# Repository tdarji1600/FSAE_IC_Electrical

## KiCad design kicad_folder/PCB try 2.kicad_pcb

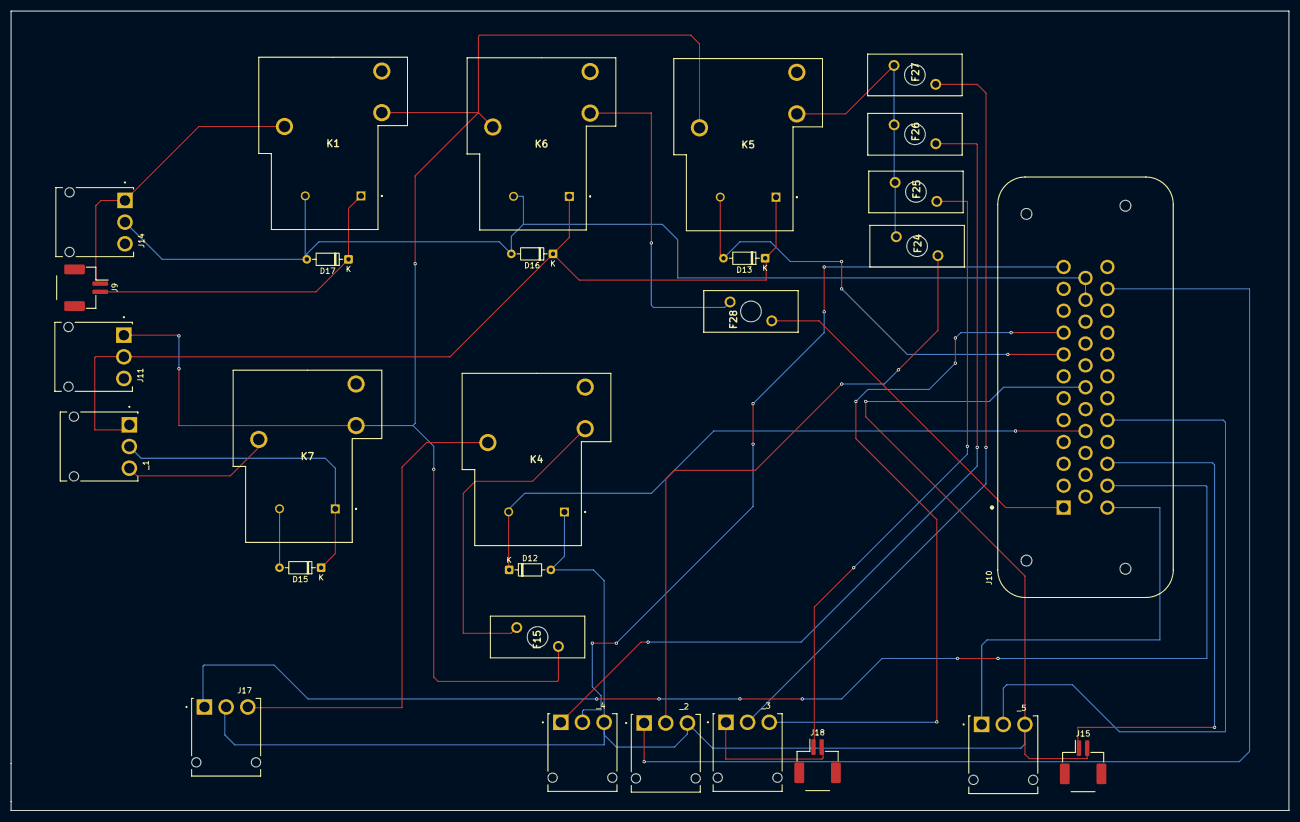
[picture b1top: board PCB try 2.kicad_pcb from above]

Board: 2 copper layers, 233.7 x 146.2 mm, 28 parts (0 on the bottom side), 28 nets.

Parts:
D12, D13, D15, D16, D17: D; D_DO-35_SOD27_P7.62mm_Horizontal
F15: Fans 5A; Little Fuse (01530008)
F24: O2 heater 10A; Little Fuse (01530008)
F25: Fuel 5A; Little Fuse (01530008)
F26: Ignition 5A; Little Fuse (01530008)
F27: Injector 5A; Little Fuse (01530008)
F28: 5A ECU fuse; Little Fuse (01530008)
J9: KillSwitches; 2 Pin Molex Click Mate
J10: ECU PINOUT; 35 Pin Ampseal
J11: Ignition; 3-Pin DF63M Connector
J14: V_in; 3-Pin DF63M Connector
J15: Intake_Air_Temp; 2 Pin Molex Click Mate
J17: Coolant_Sys; 3-Pin DF63M Connector
J18: Pingle_fuel_switch; 2 Pin Molex Click Mate
K1: Shutdown Relay; Relay( PRY412V9001CEF)
K4: Fans Relay; Relay( PRY412V9001CEF)
K5: Fuel Pump and Injectors; Relay( PRY412V9001CEF)
K6: Main Relay; Relay( PRY412V9001CEF)
K7: starter control relay; Relay( PRY412V9001CEF)
_1: starter; 3-Pin DF63M Connector
_2: O2_Sens; 3-Pin DF63M Connector
_3: FP+INJ; 3-Pin DF63M Connector
_4: Ignition_Coil; 3-Pin DF63M Connector
_5: MAP; 3-Pin DF63M Connector

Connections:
/Bridge: F15.2, J11.1, K1.2, K5.4, K6.4, K7.2
Chassis GND: D16.2 (A), D17.2 (A), J10.22, J10.23, J14.2, K1.5, K6.5
GND: D12.2 (A), J10.18, J15.2, J17.2, K4.1, _2.3, _4.3, _5.3
GNDPWR: D15.2 (A), K7.5
unnamed: D12.1 (K), J10.16, K4.5
unnamed: D13.2 (A), J10.8, K5.5
unnamed: D13.1 (K), D16.1 (K), J11.2, K5.1, K6.1, _1.1
unnamed: D15.1 (K), K7.1, _1.2
unnamed: D17.1 (K), J9.2, K1.1
unnamed: F15.1, K4.2
unnamed: F24.2, F25.2, F26.2, F27.2, K5.2
unnamed: F28.1, K6.2
unnamed: F28.2, J10.1
unnamed: J10.9, _3.3
unnamed: J10.12, _4.2
unnamed: J10.24, _5.1
unnamed: J10.25, J17.1
unnamed: J10.26, J15.1
unnamed: J10.28, _5.2
unnamed: J10.34, _2.1
unnamed: J9.1, J14.1, K1.4
unnamed: J17.3, K4.4
unnamed: F25.1, J18.1
unnamed: J18.2, _3.1
unnamed: K7.4, _1.3
unnamed: F24.1, _2.2
unnamed: F27.1, _3.2
unnamed: F26.1, _4.1
